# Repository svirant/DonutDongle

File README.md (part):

# Donut Dongle

**Arduino Nano based hub that connects your digital and analog console switching setup with the RetroTink 4K and/or RetroTink 5x / OSSC for Auto Profile switching** </br>

The Donut Dongle connects to a switch in a way that allows it to see which port is active. When a console powers on (auto-switching) or an input is manually selected, the Donut Dongle sends a serial command to the RetroTink 4k (or IR signal to the RT5x, OSSC) telling it to load a profile. For the RT4K, the profiles can either be defined as remote profiles; those configured in the menu for the remote buttons. Or they can be SVS profiles which are configured on the RT4K's SDcard. <br />

For details, refer to the ["How to Use"](https://github.com/svirant/DonutDongle/tree/main/README.md#how-to-use) section below.

> [!TIP]
> If DIY is not your thing. I have assembled versions for gScart/gComp and MT-VIKI/TESmart/Extron/db9 available in my [Ko-fi](https://ko-fi.com/donutswdad/shop) shop.
</br>

> [!NOTE]
> *NEW* version allows:
>   - **Alternate SVS Profile System** - allows a different set of profiles to load. Explained in the ["New IR Remote Control functionality"](https://github.com/svirant/DonutDongle#new-ir-remote-control-functionality) section below.
>   - **Fallback** - feature that allows a switch that reports having no active inputs to change profiles over to one that does.
>   - **MT-VIKI Disconnection Detection** - when an input is powered off and on, the profile is resent.
>     - **Disable MT-VIKI beeping by pressing the "#" button on its remote.**
>   - **front case buttons/remote NOW change profiles on the MT-VIKI HDMI switch.** Thanks to [Arthrimus](https://scalablevideoswitch.com/)! 
>   - **auto-switching on Extron Matrix switchers** that support DSVP. Works with RGBS/HV and HDMI/DVI signal types.
>   - **Support for older Extron Crosspoint (non plus) matrix switchers**
> <br />
> 
> <br /> Use the follow Options to enable:
> ```
> #define automatrixSW1 true  // set true for auto matrix switching on "SW1" port
> #define automatrixSW2 false // set true for auto matrix switching on "SW2" port
>
> uint8_t const ExtronVideoOutputPortSW1 = 1; // For non "Plus" Extron Matrix models, must specify video output port that connects to RT4K
> uint8_t const ExtronVideoOutputPortSW2 = 1;
> 
> uint8_t const vinMatrix[65] = {0,  // MATRIX switchers  // When auto matrix mode is enabled: (automatrixSW1 / SW2 defined above)
>                                                        // set to 0 for the auto switched input to tie to all outputs
>                                                        // set to 1 for the auto switched input to trigger a Preset
>                                                        // set to 2 for the auto switched input to tie to "ExtronVideoOutputPortSW1" / "ExtronVideoOutputPortSW2"
>                                                        //
>                                                        // For option 1, set the following inputs to the desired Preset #
>                                                        // (by default each input # is set to the same corresponding Preset #)
>                                                       
> ```
<br />

### [More Images...](https://photos.sixteenbit.app/share/KXUwNPO2uvjenoCdj3gsQnEMd4q5h4ymUv-0fc8PItIhjA8JXHlVgPDeFnTRXM76KPM)

<br />

# Thanks to 
 - [Justin Peacock](https://byjustin.me/) for the amazing case design
 - HerraAAV3 from the RetroTink discord for the VGA Adapter case design
 - [Mike Chi](https://retrotink.com) for help with the open drain serial bits
 - [@niquallis](https://x.com/niquallis), [@UstSte](https://x.com/UstSte), and last but not least [Aru](https://x.com/CielFricker249) for beta testing

<br />

# Supported Switches
(current list, but not limited to)
| **Switch**    | Supported | Notes |
| ------------- | ------------- |------------- |
| MT-VIKI 8 port HDMI | yes, confirmed first hand. RT4K remote can also change inputs and profiles.  | Front case buttons and included IR remote also change profiles! **Disable MT-VIKI beeping by pressing the "#" button on its remote.** |
| TESmart 16x1 HDMI  | yes, confirmed first hand  | RT4K remote can also change inputs and profiles. |
| TESmart 8x1 HDMI  | unconfirmed, but should work, let me know! ||
| gSCARTsw / gCOMPsw | **version 5.x** confirmed by [@niquallis](https://x.com/niquallis) and [@UstSte](https://x.com/UstSte), thanks so much for your help! | Manual input selection works too! |
| Extron RGBHV sw6  | yes, confirmed first hand  | |
| Extron DXP 88 | yes, confirmed first hand | Auto-switching can be enabled in "Options" section of .ino.  Works with Presets. On SW1, Preset 1 is S1_ profile. On SW2, Preset 1 is S101_ profile, etc. <br><br>Power up the switch before connecting the DonutHole. |
| Extron CrossPoint, MVX, etc | yes, confirmed by other users | Auto-switching can be enabled for switches that supports DSVP and are RGBS/HDMI/DVI signal types. By default, works with Presets as shown in the Note above. |
| Extron CrossPoint E-series  | yes, works with Presets and Input changes | Must set ExtronVideoOutputPortSW1 / SW2 variable to output connected to RT4K |
| Extron SW4 VGA Ars | yes, confirmed by "Nobody" on the RT4K Discord |
| Otaku Games Scart 10 | Jumper moved to "L" and with required [mod](https://github.com/svirant/RT4k_HD15_serial_control/tree/main/Otaku%20Games%20Scart%20Switch) , **SVS=0; must also be set in the Otaku .ino for the DD to respond** | modded switch works on its own, but connecting through the DD is mostly useful if your Otaku mod doesn't include the buffer IC |

<br />

# Connections
  - Connect 4 switches Total
    - 2x gscart/gcomp
    - 2x Extron, 2x TESmart, or 1 of each
  - 1x usb-c port for power/programming (on Arduino Nano)
  - 1x 3.5mm "TX OUT to Retrotink 4K VGA adapter" port
  - 1x IR Emitter (required for OSSC, RT5x (RT5x must be on firmware version 3.7 or higher))
  - 1x IR Receiver (optional for better reception and IR remote customizations)

<br /><br />

# Layout Example
 - **TESmart 16x1 HDMI switch & 2x gSCART/gCOMP**
    - **VGA Passthrough adapter**
    - **TESmart adapter**
    - **gScart EXT pushpin adapter**

<br />
<br />

 - **Case closed**
   - **ribbon cables fold over and come out slots in the back of case**

<br /><br />

# Connection Acccessories

**gscart/gcomp EXT connector (plug-n-play)**<br />
The spring pins allow it to stay "sandwiched" in place by the lid<br />

<br />

**TESmart connector**<br />

**MT-VIKI / Extron / DB9 adapter**<br />

**Parts listed in [BOM](https://github.com/svirant/DonutDongle/tree/main/README.md#connection-accessories) below**

**Alternate Extron connection type:**
   - **DB9 male to 3.5mm (connects to alt sw1 / alt sw2 port instead of 2x5 header)**
   - **Higher quality and much longer cord than the standard 2x5 cable**

----------------
# New IR Remote Control functionality
When using the optional IR Receiver, the IR reception of the RT4K can be been greatly enhanced. You can think of it as an IR repeater, but instead talks to the RT4K via Serial for solid communication. Since the Donut Dongle is in the middle, other remote features can be added such as:
 - **Alternate SVS Profiles**: Have you ever wanted to add CRT effects to all of your existing SVS profiles? Or wanted all your profiles to output at 1080p instead of 4K? With this feature you can create a set of SVS profiles that have these changes and activate the system with the remote. Pressing the "SAFE" button twice + 1 - 9 buttons will allow you to configure 9 different sets of these profiles per regular profile to load instead of the regular one you created. For example: Instead of SVS profile S1_SNES.rt4 loading, S1001_SNES.rt4 will load instead after activating with the "SAFE"x2 + 1 button. Here are some more examples so you can see the pattern used for creating these: </br>

    "SAFE"x2 + x button = Sx001_SNES-CRT.rt4, where x is the number button selected and 001 is the S1_ profile represented in 3 digits. </br>
    "SAFE"x2 + 2 button = S2001_SNES-1080p.rt4 </br>
    "SAFE"x2 + 3 button = S3001_SNES-Zoomed.rt4 </br>
    "SAFE"x2 + 4 button = S4001_SNES.rt4 </br>
    "SAFE"x2 + 5 button = S5001_SNES.rt4 </br>
    "SAFE"x2 + 6 button = S6001_SNES.rt4 </br>
    "SAFE"x2 + 7 button = S7001_SNES.rt4 </br>
    "SAFE"x2 + 8 button = S8001_SNES.rt4 </br>
    "SAFE"x2 + 9 button = S9001_SNES.rt4 </br> 

   - The name following the "\_" can be changed as well. So a name like S1001_SNES-CRT.rt4 can be used to better describe. Only the naming pattern before the "\_" is important. </br>

   - When SVS profile S2 normally would load, Sx002 would load instead where x = the number button chosen prior and 002 represents the S2 profile. S2100_NES.rt4 for example would be the 2nd Alternate profile for S100_NES.rt4. It's up to you to create these alternate sets of profiles on your SD card of course. To disable this feature and return to your normally configured profiles, press "SAFE"x2  + 10, 11, or 12 buttons on the remote.

 - SAFE button once + profile button 1 - 12 loads SVS profiles of your choosing. By default is SVS 1 - 12. Configured with auxprof[] in the Settings section of the .ino
  
 - Normally, if you power on your console before waking the RT4K, the RT4K will have not seen the profile change. Using the remote's POWER button, in this configuration, will wake the RT4K "and" resend the profile after it's finished waking.

 - AUX8 button + Power button power cycles your TV via IR Emitter. (only LG OLED CX atm, more can be added upon request)

 - AUX8 pressed twice, manually enter a SVS profile to load with the profile buttons using 1 - 9 and 10,11,12 buttons for 0. Must use 3 digits. Ex: 001 = 1, 010 = 10, etc

 - AUX8 pressed 3x will perform the standard AUX8 action
 
 - MT-ViKI 8 Port HDMI switch's inputs can be changed. Must configure "MTVir" in the options section of the .ino
    - AUX7 + button 1 - 8 for inputs 1 - 8 on "alt sw1" port (SVS profiles 1 - 8)
    - AUX8 + button 1 - 8 for inputs 1 - 8 on "alt sw2" port (SVS profiles 101 - 108)

 - TESmart 16x1 HDMI switch's inputs can changed. Must set "TESmartir" in the options section.
    - AUX7 + button 1 - 12, aux1, aux2, aux3, aux4 for inputs 1 - 16 on "alt sw1" port (SVS profiles 1 - 16)
    - AUX8 + button 1 - 12, aux1,aux2,aux3,aux4 for inputs 1 - 16 on "alt sw2" port (SVS profiles 101 - 116)

**gScart / gComp Control** (must set gctl = 1 in Options, Only supported on vers 5.x switches)

 - AUX5 button + profile button 1 - 8 button selects corresponding input on gscart sw1
    - AUX5 button + profile button 9 - 12 button to return to auto switching

 - AUX6 button + profile button 1 - 8 button selects corresponding input on gscart sw2
    - AUX6 button + profile button 9 - 12 button to return to auto switching

 - RT5x and OSSC may require a repeat of the button combos
 
 <br />

Let me know what ideas you have, and perhaps I can add them in.

**Note:** To stop the RT4K from responding twice (once from the built-in IR sensor and once from the Donut Dongle), place the included "ir_remote.txt" on the root of the SDcard. This remaps the builtin IR for every button except POWER to the RT5x remote. This way you can still use the POWER button to power on the RT4K but will stop it from responding from all other button presses.

# Ordering PCBs
PCBs for this project:
 - [Donut Dongle](https://github.com/svirant/DonutDongle/blob/main/RT4K_donut_dongle.zip)
 - [VGA Adapter](https://github.com/svirant/DonutDongle/tree/main/Adapters) (VGAPassthrough or YC2VGA)
 - (Optional) [TESmart_connector](https://github.com/svirant/DonutDongle/tree/main/Accessories)
 - (Optional) [gscart_ext_connector](https://github.com/svirant/DonutDongle/tree/main/Accessories) (works for gcomp too!)
 
There are plenty of options for PCB manufacturing but I prefer [JLCPCB](https://jlcpcb.com) (No affiliation). Using the gerber (.zip) files provided, it's easy to place an order. Below are some tips/guidelines:
- 1.0mm PCB Thickness for gscart_ext_connector.zip
- 1.6mm for all others
- For Surface Finish, "HASL(with lead)" is fine
- 4 Layer PCBs are the same cost as 2 Layer for the VGA Adapters. Because of that, the inner 2 layers are being used as ground planes for better EMI protection. Thanks to https://x.com/zaxour for the idea!
- "Remove Mark" option is now free on JLCPCB. Use it!
- All remaining default options should be fine
- Let me know if you have any questions!

# Assembly
**v1.0**<br /><br />
[Interactive HTML BOM](https://svirant.github.io/DonutDongle/images/ibom.html)

# (2M) baud mod
- **NOT supported with SVS connected to VGA adapter**
  - ...unless SDA/SDL trace is cut on VGA Adapter, but that disables the SVS's profile sending.
  - SVS runs at 9600 baud which conflicts with 2M regardless.
  - Extra Tx/Rx wire length of VGA cable can also cause issues. Workaround - You can cut SDA/SDL traces on the bottom of the VGA adapter to continue passing video but disables "VGA cable Serial" passthrough. (How the SVS sends profile changes)

  <br>
- Replace R10 (10K) with a 2.2K resistor
- Remove R9 and bridge pads
- Connect R1 and R9 as shown with a 2.2K resistor
<br><br>

# PCB
**v1.0**

<br /><br />

# Schematic
**v1.0**

<br /><br />

## Bill of Materials (BOM)
### [- 3D Printed Dount Dongle Case](https://makerworld.com/en/models/1154283#profileId-1159282)
### [- 3D Printed VGA Adapter Case](https://github.com/svirant/DonutDongle/tree/main/Adapters) [Courtesy of HerraAAV3 on the RetroTink Discord]
### [- Digikey shared list](https://www.digikey.com/en/mylists/list/53XEHTQZJK)
### [- AliExpress wish list](https://www.aliexpress.com/p/wish-manage/share.html?smbPageCode=wishlist-amp&spreadId=09A40E28BA67E42DE9AF29A70E7238263DE305046632ABE9A0D5E1C5C4589AD9)
<br />

* **Donut Dongle PCB**

| **Qty**    | Designation | Part |  Link  |  Notes |
| ------------- | ------------- |------------- |------------- |------------- |
| 2  | C1,C5 | 0.1 uf / 100nf 50V X7R 0805 Capacitor| [Digikey](https://www.digikey.com/en/products/detail/yageo/CC0805KRX7R9BB104/302874?s=N4IgTCBcDaIMwEYEFokBYAMrkDkAiIAugL5A) | |
| 3  | C2-C4 | 0.33 uf / 330nf 50V X7R 0805 Capacitor| [Digikey](https://www.digikey.com/en/products/detail/samsung-electro-mechanics/CL21B334KBFNNNE/3886781) | |
| 1  | R1 | 30 OHM 1% 1/2W 0805 Resistor | [Digikey](https://www.digikey.com/en/products/detail/panasonic-electronic-components/ERJ-P06F30R0V/9811718) | |
| 1  | R2 | 1K OHM 1% 1/8W 0805 Resistor | [Digikey](https://www.digikey.com/en/products/detail/yageo/RC0805FR-071KL/727444) | |
| 10  | R3 - R10, R17, R19 | 10K OHM 1% 1/8W 0805 Resistor | [Digikey](https://www.digikey.com/en/products/detail/yageo/AC0805FR-0710KL/2827834) | |
| 8  | R11 - R16, R18, R20 | 20K OHM 1% 1/8W 0805 Resistor | [Digikey](https://www.digikey.com/en/products/detail/yageo/RC0805FR-0720KL/727720) | |
| 1  | Q1 | 2N3904 NPN Transistor | [AliExpress](https://www.aliexpress.us/item/3256806623522970.html) | |
| 1  | U1 | MAX3232 SOP-16 RS-232 Interface IC | [AliExpress](https://www.aliexpress.us/item/3256807314260762.html) | |
| 1  | U2 | IC BUF NON-INVERT 5.5V SOT23-6 | [Digikey](https://www.digikey.com/en/products/detail/texas-instruments/SN74LVC2G07DBVR/486427) or [alternate](https://www.digikey.com/en/products/detail/umw/SN74LVC2G07DBVR/24889644)| |
| 1  | PH1 | PJ-307 3.5mm Stereo Jack | [AliExpress](https://www.aliexpress.us/item/3256805624175150.html) | |
|    | |  or **1x** 3.5mm Audio Jack Socket | [AliExpress](https://www.aliexpress.us/item/2251832685563184.html) | Like the PJ-307 but missing the inner 2 poles which arent needed anyways |
| 4  | J4,J9-11 | PJ-320 3.5MM Headphone Jack Audio Video Female | [AliExpress](https://www.aliexpress.us/item/3256807448104402.html) | Color: PJ-320B DIP | 
| 2  | J3,J6 | 2x5 Pin Double Row 2.54mm Pitch Straight Box Header | [AliExpress](https://www.aliexpress.us/item/3256805177947724.html) | (Color: STRAIGHT TYPE, Pins: 10PCS DC3-10Pin) |
| 2  | J5,J8 | 2x4 Pin Double Row 2.54mm Pitch Straight Box Header | [AliExpress](https://www.aliexpress.us/item/3256805177947724.html) | (Color: STRAIGHT TYPE, Pins: 10PCS DC3-8Pin) |
| 1  | (optional) | 3.5mm CHF03 1.5 Meters IR Infrared Remote Emission Cable | [AliExpress](https://www.aliexpress.us/item/3256805962345169.html) | required for OSSC, RT5X (must be firmware version 3.7+) |
| 1  | (optional) | 3.5mm Infrared Remote Control Receiver Extension Cable | [AliExpress](https://www.aliexpress.us/item/2251832741040177.html) | required for [New IR Remote Control functionality](https://github.com/svirant/DonutDongle?tab=readme-ov-file#new-ir-remote-control-functionality) |
| 2  | H1,H2 | 2.54mm Pitch Single Row Female 15P Header Strip | [AliExpress](https://www.aliexpress.us/item/3256801232229618.html) | |
| 1  | | Any 3.5mm / aux / stereo / trs / cable | [AliExpress](https://www.aliexpress.us/item/2255799962255486.html) | |
| 1  | | usb-c cable for Arduino power & initial programming | [AliExpress](https://www.aliexpress.us/item/3256806983355947.html) | |
| 1  | | Arduino Nano type c | Support [RetroRGB!](https://amzn.to/4gnHqN4) | Make sure the headers and esp the 2x3 pins are not soldered. |
| 1  | JP2 | 2x3 Pin Double Row 2.54mm Pitch Header | | Use the one that comes with the Arduino Nano. Jumper "H" for all switches unless instructed otherwise. |
| 2  | JP3,4 | 1x3 Pin Single Row 2.54 Pitch Header | | Dont buy two 1x3. Find any single row header and break off two 1x3 sections. Jumper "H" for all switches unless instructed otherwise. |
| 4  | | 2.54mm Jumper | [AliExpress](https://www.aliexpress.us/item/2255800354403384.html) | You can also just solder blob "H". "L" jumper setting has only 1 use case atm. |

* **Switch connection Cables**

| **Qty**    | Switch Type | Part |  Link  |  Notes |
| ------------- | ------------- |------------- |------------- |------------- |
| 1 or 2 | **TESmart HDMI** | Any 3.5mm / aux / stereo / trs / Cable | [AliExpress](https://www.aliexpress.us/item/2255799962255486.html) | strip 1 end to expose red(Rx)/white(Tx)/gnd wires for the green screw clamp OR use the TESmart_connector shown below|
| 1 or 2 | **GscartSW/GCompSW** | 2x4 Pin Double Row 2.54 Pitch Angled Box Header | [AliExpress](https://www.aliexpress.us/item/3256805177947724.html?) | (Color: RIGHT ANGLE TYPE, Pins: 10PCS DC3 8Pin), Solders onto EXT port. Or use the gscart_ext_connector shown below.  |
|1 or 2 | **GscartSW/GCompSW** | 2x4 Pin Female Header Ribbon Cable | [AliExpress](https://www.aliexpress.us/item/3256804576275377.html?) | (Pins: 2x4Pin, Color: Any length) |
| 1  | **Extron** | 2 Port DB9 to 2x5 Pin Female Header Ribbon Cable | [AliExpress](https://www.aliexpress.us/item/3256807472891897.html) | |
| | | or **2x** DB9 Male to 3.5mm Male Serial RS232 Cable 6feet | [Amazon](https://www.amazon.com/LIANSHU-DC3-5mm-Serial-RS232-Cable/dp/B07G2ZL3SL/) | "MUST" be wired as so: [DB9 Male Pin 5 -> Sleeve, DB9 Male Pin 2 -> Tip, DB9 Male Pin 3 -> Ring](/images/7.png) |
| | | **or** make your own connectors in the "[Connection Accessories](https://github.com/svirant/DonutDongle?tab=readme-ov-file#connection-accessories-optional)" section below. | | |

### At least 1 of the following [VGA adapters](https://github.com/svirant/DonutDongle/tree/main/Adapters) is required:

* **YC2VGA w/ Serial Tap v2: (enhanced s-video and composite as a bonus)**

<br />

| **Qty**    | Part |  Link  |  Notes |
| ------------- | ------------- |------------- |------------- |
| 1  | Yellow RCA Composite jack | [AliExpress](https://www.aliexpress.us/item/3256805949533421.html) | (Color: Yellow) |
| 1  | S-Video jack | [AliExpress](https://www.aliexpress.us/item/3256804041313042.html) | (Color: A 4Pin) |
| 1  | PJ-320 3.5MM Headphone Jack Audio Video Female | [AliExpress](https://www.aliexpress.us/item/3256805995568762.html) | (Color: 10PCS PJ-320) |
| 1  | VGA Male Connector [L717HDE15PD4CH4R-ND] | [Digikey](https://www.digikey.com/en/products/detail/amphenol-cs-commercial-products/L717HDE15PD4CH4R/4886543) | |
 
* **VGA Passthrough w/ Shared Serial Tap:**
   - Confirmed compatible with the Scalable Video Switch and it's auto profiles.

<br />

<br />

| **Qty**    | Part |  Link  |  Notes |
| ------------- | ------------- |------------- |------------- |
| 1 | VGA Male Connector [L717HDE15PD4CH4R-ND] | [Digikey](https://www.digikey.com/en/products/detail/amphenol-cs-commercial-products/L717HDE15PD4CH4R/4886543) | |
| 1 | VGA Female Connector | [AliExpress](https://www.aliexpress.us/item/3256807197056325.html) | (Color: DB15 3.08) |
| 1 | PJ-320 3.5MM Headphone Jack Audio Video Female | [AliExpress](https://www.aliexpress.us/item/3256805995568762.html) | (Color: 10PCS PJ-320) |
| 2 | #4-40 x 3/4" screw (optional) | [Ebay](https://www.ebay.com/itm/222577369468) | |

  ### [Connection Accessories](https://github.com/svirant/DonutDongle/tree/main/Accessories) (optional)

  * **gscart/gcomp EXT connector**

| **Qty**    | Part |  Link  |  Notes |
| ------------- | ------------- |------------- |------------- |
| 1 | 2x4 Pin Double Row 2.54 Pitch Angled Box Header | [AliExpress](https://www.aliexpress.us/item/3256805177947724.html?) | (Color: RIGHT ANGLE TYPE, Pins: 10PCS DC3 8Pin) |
| 6 | Pogo-Pin | [Digikey](https://www.digikey.com/en/products/detail/mill-max-manufacturing-corp/0906-1-15-20-75-14-11-0/1147049) | |
   
  * **TESmart connector**

 | **Qty**    | Part |  Link  |  Notes |
| ------------- | ------------- |------------- |------------- |
| 1 | PJ-320 3.5MM Headphone Jack Audio Video Female | [AliExpress](https://www.aliexpress.us/item/3256805995568762.html) | (Color: 10PCS PJ-320) |

  * **MT-VIKI / Extron / DB9 connector**

 | **Qty**    | Part |  Link  |  Notes |
| ------------- | ------------- |------------- |------------- |
| 1 | PJ-320 3.5MM Headphone Jack Audio Video Female | [AliExpress](https://www.aliexpress.us/item/3256805995568762.html) | (Color: 10PCS PJ-320) |
| 1 | DB9 Male connector | [AliExpress](https://www.aliexpress.us/item/3256805749759770.html?) | (Color: Male head) |
| 2 | #4-40 1/4" pan head screw | [Amazon](https://www.amazon.com/dp/B00F34USTG?) | |

  -----------
# Programming an Arduino Nano
I recommend the [Official Arduino IDE and guide](https://www.arduino.cc/en/software/) if you're unfamiliar with Arduinos. All .ino files used for programming are listed above. The following Libraries will also need to be added in order to Compile successfully.<br />
- **Libraries:**
  - <IRremote.hpp> "IRremote" available through the built-in Library Manager under "Tools" -> "Manage Libraries..."
  - <AltSoftSerial.h>  Follow these steps to add AltSoftSerial.h
    - Goto https://github.com/PaulStoffregen/AltSoftSerial
    - Click the GREEN "<> Code" box and "Download ZIP"
    - In Arduino IDE; goto "Sketch" -> "Include Library" -> "Add .ZIP Library"
   
## Steps to program the Donut Dongle
 - 1 - Click the green "<> Code" button above and "Download ZIP".
 - 2 - Extract the .zip file and open up the "Donut_Dongle.ino" file in the Arduino IDE. It will ask if you would like to move this file inside a folder, select OK.
 - 3 - With the source code now open, select "Tools" -> "Board" -> "Arduino AVR Boards" -> "Arduino Nano"
 - 4 - Connect the Donut Dongle device to your PC or Mac using the usb-c cable. You should see an LED light up when connected.
 - 5 - With the Donut Dongle now connected, select it's "port" by going to "Tools" -> "Port", and select the port that starts with "/dev/cu.usbserial-" (on Mac) or "COM" if on PC.
 - 6 - From the menu at the top, select "Sketch" -> "Verify/Compile". If everything is setup properly, you should see a message in the bottom corner saying "Done compiling".
 - 7 - Now select "Sketch" -> "Upload". You should see the LEDs on the Donut Dongle flicker and a message that says "Done uploading." if successful.
   - If you get errors, see the section below about changing the "Bootloader" type.
 - 8 - Disconnect the usb-c cable from your computer and give it a whirl! You can repeat these steps in the future to make any other changes or update if a newer firmware is ever released.
 - 9 - It's also best practice when unplugging/reconnecting cables to the Donut Dongle, that you do so with the power disconnected. 
<br>

  -----------
# How to Use
- Make sure **"Auto Load SVS"** is **"On"** under the RT4K Profiles menu.  
- The RT4K checks the **/profile/SVS** subfolder for profiles and need to be named: **S\<input number>_\<user defined>.rt4**  For example, SVS input 2 would look for a profile that is named S2_SNES.rt4.  If there’s more than one profile that fits the pattern, the first match is used.

- Check the RT4K Diagnostic Console for Serial commands being received as confirmation.

  -----------
# Troubleshooting
 - When (un)plugging aux cables from "alt sw1" or "alt sw2" ports make sure Donut Dongle power is disconnected. Sometimes the onboard MAX3232 chip can lock up if this is not done.
   - To fix lockup, power off switch and DD (Donut Dongle). Disconnect/reconnect aux cable from DD and power up switch first, then DD last.
  
 - Some Arduino Nanos come with an Old Bootloader and won't Upload unless specified. **If you get errors** when trying to upload, swap to this option as a possible fix.

  -----------
## SVS Profile numbering scheme

| **SVS = 1 (default)** | **Profile #** | Notes |
|----------|----------|---------|
| Extron sw1 / alt sw1 | 1 -  99 | also for TESmart, MT-ViKi, Otaku Games Scart 10 devices|
| Extron sw2 / alt sw2 | 101 - 199 | also for TESmart, MT-ViKi, Otaku Games Scart 10 devices |
| GSCART sw1 | 201 - 208 | |
| GSCART sw2 | 209 - 216 | |

Remote Button Profiles are **not** used when **SVS=1**

<br />

| **SVS = 0** | **Profile #** | Notes |
|----------|----------|---------|
| Extron sw1 / alt sw1 | 13 -  99 | also for TESmart, MT-ViKi, Otaku Games Scart 10 devices|
| Extron sw2 / alt sw2 | 101 - 199 | also for TESmart, MT-ViKi, Otaku Games Scart 10 devices |
| GSCART sw1 | 201 - 208 | |
| GSCART sw2 | 209 - 216 | |

Remote Button Profiles **1-12** are used for Extron sw1 when **SVS=0**

<br />

| **SVS = 2** | **Profile #** | Notes |
|----------|----------|---------|
| Extron sw1 / alt sw1 | 1 -  99 | also for TESmart, MT-ViKi, Otaku Games Scart 10 devices|
| Extron sw2 / alt sw2 | 101 - 199 | also for TESmart, MT-ViKi, Otaku Games Scart 10 devices |
| GSCART sw1 | N/A | |
| GSCART sw2 | 213 - 216 | inputs 5-8 |

Remote Button Profiles **1-12** are used for GSCART sw1 inputs **1-8** and GSCART sw2 inputs **1-4** when **SVS=2**

<br />

----------------

The following is from the .ino file itself. Refer to it directly for all **Advanced Options**.
```
/*
////////////////////
//    OPTIONS    //
//////////////////
*/

uint8_t const debugE1CAP = 0; // line ~495
uint8_t const debugE2CAP = 0; // line ~768
uint8_t const debugState = 0; // line ~432

uint16_t const offset = 0; // Only needed for multiple Donut Dongles (DD). Set offset so 2nd,3rd,etc boards don't overlap SVS profiles. (e.g. offset = 300;) 
                      // MUST use SVS=1 on additional DDs. If using the IR receiver, recommended to have it only connected to the DD with lowest offset.

uint8_t const SVS = 1; //     "Remote" profiles are profiles that are assigned to buttons 1-12 on the RT4K remote. "SVS" profiles reside under the "/profile/SVS/" directory 
                      //     on the SD card.  This option allows you to choose which ones to call when a console is powered on.  Remote profiles allow you to easily change 
                      //     the profile being used for a console's switch input if your setup is in flux. SVS require you to rename the file itself on the SD card which is 
                      //     a little more work.  Regardless, SVS profiles will need to be used for console switch inputs over 12.
                      //
                      // **** Make sure "Auto Load SVS" is "On" under the RT4K Profiles menu. A requirement for most options ****
                      //
                      // 0 - use "Remote" profiles 1-12 for up to 12 inputs on 1st Extron Switch and SVS 13 - 99 for everything over 12. Only SVS profiles are used on 2nd Extron Switch if connected.
                      //
                      //     - remote profiles 1-12 for 1st Extron or TESmart Switch (If S0 below is set to true - remote profile 12 is used when all ports are in-active)
                      //     - SVS  12 - 99  for 1st Extron or TESmart (S0 is true)
                      //     - SVS  13 - 99  for 1st Extron or TESmart (S0 is false)
                      //     - SVS 101 - 199 for 2nd Extron or TESmart
                      //     - SVS 201 - 208 for 1st gScart
                      //     - SVS 209 - 216 for 2nd gScart
                      //
                      // 1 - use only "SVS" profiles.
                      //     Make sure "Auto Load SVS" is "On" under the RT4K Profiles menu
                      //     RT4K checks the /profile/SVS subfolder for profiles and need to be named: "S<input number>_<user defined>.rt4"
                      //     For example, SVS input 2 would look for a profile that is named S2_SNES.rt4
                      //     If there’s more than one profile that fits the pattern, the first match is used
                      //
                      //     - SVS   1 -  99 for 1st Extron or TESmart
                      //     - SVS 101 - 199 for 2nd Extron or TESmart
                      //     - SVS 201 - 208 for 1st gScart
                      //     - SVS 209 - 216 for 2nd gScart
                      //     - SVS   0       for S0 option mentioned below
                      //
                      //  ** If S0 below is set to true, create "/profile/SVS/S0_<user defined>.rt4" for when all ports are in-active. Ex: S0_HDMI.rt4
                      //
                      // 2 - use "Remote" profiles 1-12 for gscart/gcomp switches. Remote profile 1-8 for 1st gscart switch, 9-12 for inputs 1-4 on 2nd gscart switch.
                      //     inputs 5-8 on the 2nd gscart switch will use SVS profiles 213 - 216
                      //
                      //     - remote profiles 1-8 for 1st gScart, 9 - 12 for first 4 inputs on 2nd gScart (If S0 below is set to true - remote profile 12 is used when all ports are in-active)
                      //     - SVS 213 -  216 for remaining inputs 5 - 8 on 2nd gScart 
                      //     - SVS   1 -  99 for 1st Extron or TESmart
                      //     - SVS 101 - 199 for 2nd Extron or TESmart
                      //

bool const S0 = false;  // (Profile 0) default is false
                         //
                         //  ** Recommended to remove any /profile/SVS/S0_<user defined>.rt4 profiles and leave this option set false if using in tandem with the Scalable Video Switch. **
                         //  ** Does not work with TESmart HDMI switches **
                         //
                         // For SVS=0; set true to load "Remote Profile 12" when all ports are in-active on SW1 (and SW2 if connected). 
                         // You can assign it to a generic HDMI profile for example.
                         // If your device has a 12th input, SVS will be used instead. "If" you also have an active 2nd Extron Switch, Remote Profile 12
                         // will only load if "BOTH" switches have all in-active ports.
                         // 
                         // For SVS=1, /profile/SVS/ "S0_<user defined>.rt4" will load instead of Remote Profile 12
                         //
                         // For SVS=2, Remote Profile 12 will be used instead of "S0_<user defined>.rt4"
                         //

////////////////////////// 
                        // Choosing the above two options can get quite confusing (even for myself) so maybe this will help a little more:
                        //
                        // when S0=0 and SVS=0, button profiles 1 - 12 are used for EXTRON sw1, and SVS for EVERYTHING else
                        // when S0=0 and SVS=1, SVS profiles are used for everything
                        // when S0=0 and SVS=2, button profiles 1 - 8 are used for GSCART sw1, 9 - 12 for GSCART sw2 (ports 1 - 4), and SVS for EVERYTHING else
                        // when S0=1 and SVS=0, button profiles 1 - 11 are used for EXTRON sw1 and Remote Profile 12 as "Profile S0", and SVS for everything else 
                        // when S0=1 and SVS=1, SVS profiles for everything, and uses S0_<user defined>.rt4 as "Profile 0" 
                        // when S0=1 and SVS=2, button profiles 1 - 8 are used for GSCART sw1, 9 - 11 for GSCART sw2 (ports 1 - 3) and Remote Profile 12 as "Profile S0", and SVS for EVERYTHING else
                        //
//////////////////////////

// For Extron Matrix switches that support DSVP. RGBS and HDMI/DVI video types.

#define automatrixSW1 false // set true for auto matrix switching on "SW1" port
#define automatrixSW2 false // set true for auto matrix switching on "SW2" port

///////////////////////////////

uint8_t const ExtronVideoOutputPortSW1 = 1; // For certain Extron Matrix models, must specify the video output port that connects to RT4K
uint8_t const ExtronVideoOutputPortSW2 = 1; // can also be used for auto matrix mode as shown in next option

///////////////////////////////

uint8_t const vinMatrix[65] = {0,  // MATRIX switchers  // When auto matrix mode is enabled: (automatrixSW1 / SW2 defined above)
                                                        // set to 0 for the auto switched input to tie to all outputs
                                                        // set to 1 for the auto switched input to trigger a Preset
                                                        // set to 2 for the auto switched input to tie to "ExtronVideoOutputPortSW1" / "ExtronVideoOutputPortSW2"
                                                        //
                                                        // For option 1, set the following inputs to the desired Preset #
                                                        // (by default each input # is set to the same corresponding Preset #)
                           1,  // input 1 SW1
                           2,  // input 2
                           3,  // input 3
                           4,  // input 4
                           5,  // input 5
                           6,  // input 6
                           7,  // input 7
                           8,  // input 8
                           9,  // input 9
                           10,  // input 10
                           11,  // input 11
                           12,  // input 12
                           13,  // input 13
                           14,  // input 14
                           15,  // input 15
                           16,  // input 16
                           17,  // input 17
                           18,  // input 18
                           19,  // input 19
                           20,  // input 20
                           21,  // input 21
                           22,  // input 22
                           23,  // input 23
                           24,  // input 24
                           25,  // input 25
                           26,  // input 26
                           27,  // input 27
                           28,  // input 28
                           29,  // input 29
                           30,  // input 30
                           30,  // input 31
                           30,  // input 32
                               //
                               // ONLY USE FOR 2ND MATRIX SWITCH on SW2
                           1,  // 2ND MATRIX SWITCH input 1 SW2
                           2,  // 2ND MATRIX SWITCH input 2
                           3,  // 2ND MATRIX SWITCH input 3
                           4,  // 2ND MATRIX SWITCH input 4
                           5,  // 2ND MATRIX SWITCH input 5
                           6,  // 2ND MATRIX SWITCH input 6
                           7,  // 2ND MATRIX SWITCH input 7
                           8,  // 2ND MATRIX SWITCH input 8
                           9,  // 2ND MATRIX SWITCH input 9
                           10,  // 2ND MATRIX SWITCH input 10
                           11,  // 2ND MATRIX SWITCH input 11
                           12,  // 2ND MATRIX SWITCH input 12
                           13,  // 2ND MATRIX SWITCH input 13
                           14,  // 2ND MATRIX SWITCH input 14
                           15,  // 2ND MATRIX SWITCH input 15
                           16,  // 2ND MATRIX SWITCH input 16
                           17,  // 2ND MATRIX SWITCH input 17
                           18,  // 2ND MATRIX SWITCH input 18
                           19,  // 2ND MATRIX SWITCH input 19
                           20,  // 2ND MATRIX SWITCH input 20
                           21,  // 2ND MATRIX SWITCH input 21
                           22,  // 2ND MATRIX SWITCH input 22
                           23,  // 2ND MATRIX SWITCH input 23
                           24,  // 2ND MATRIX SWITCH input 24
                           25,  // 2ND MATRIX SWITCH input 25
                           26,  // 2ND MATRIX SWITCH input 26
                           27,  // 2ND MATRIX SWITCH input 27
                           28,  // 2ND MATRIX SWITCH input 28
                           29,  // 2ND MATRIX SWITCH input 29
                           30,  // 2ND MATRIX SWITCH input 30
                           30,  // 2ND MATRIX SWITCH input 31
                           30,  // 2ND MATRIX SWITCH input 32
                           };

                           // ** Must be on firmware version 3.7 or higher **
uint8_t const RT5Xir = 0;     // 0 = disables IR Emitter for RetroTink 5x
                              // 1 = enabled for Extron sw1 / alt sw1, TESmart HDMI, MT-ViKi, or Otaku Games Scart Switch if connected
                              //     sends Profile 1 - 10 commands to RetroTink 5x. Must have IR LED emitter connected.
                              //
                              // 2 = enabled for gscart switch only (remote profiles 1-8 for first gscart, 9-10 for first 2 inputs on second gscart)
                              //
                              // 3 = enabled for Extron sw2 / alt sw2, TESmart HDMI, MT-ViKi, or Otaku Games Scart Switch if connected 
                              //     sends Profile 1 - 10 commands to RetroTink 5x. Must have IR LED emitter connected.

uint8_t const OSSCir = 0;     // 0 = disables IR Emitter for OSSC
                              // 1 = enabled for Extron sw1 switch, TESmart HDMI, or Otaku Games Scart Switch if connected
                              //     sends Profile 1 - 14 commands to OSSC. Must have IR LED emitter connected.
                              //     
                              // 2 = enabled for gscart switch only (remote profiles 1-8 for first gscart, 9-14 for first 6 inputs on second gscart)

uint8_t const MTVir = 0;   // Must have IR "Receiver" connected to the Donut Dongle for option 1 & 2.
                              // 0 = disables IR Receiver -> Serial Control for MT-VIKI 8 Port HDMI switch
                              //
                              // 1 = MT-VIKI 8 Port HDMI switch connected to "Extron sw1"
                              //     Using the RT4K Remote w/ the IR Receiver, AUX8 + profile button changes the MT-VIKI Input over Serial.
                              //     Sends auxprof SVS profiles listed below.
                              //
                              // 2 = MT-VIKI 8 Port HDMI switch connected to "Extron sw2"
                              //     Using the RT4K Remote w/ the IR Receiver, AUX8 + profile button changes the MT-VIKI Input over Serial.
                              //     Sends auxprof SVS profiles listed below. You can change them below to 101 - 108 to prevent SVS profile conflicts if needed.
                              // 3 = MT-VIKI 8 Port HDMI switch connected to BOTH "alt sw1" and "alt sw2"
                              //     Use AUX7 and AUX8 buttons as described above.
                              //

uint8_t const TESmartir = 0;  // Must have IR "Receiver" connected to the Donut Dongle for option 1 and above.
                              // 0 = disables IR Receiver -> Serial Control for TESmart 16x1 Port HDMI switch
                              //
                              // 1 = TESmart 16x1 HDMI switch connected to "alt sw1"
                              //     Using the RT4K Remote w/ the IR Receiver, AUX7 + profile button changes the Input over Serial. AUX7 + AUX1 - AUX4 for Input 13 - 16.
                              //     Sends SVS profile 1 - 16 as well.
                              //
                              // 2 = TESmart 16x1 HDMI switch connected to "alt sw2"
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
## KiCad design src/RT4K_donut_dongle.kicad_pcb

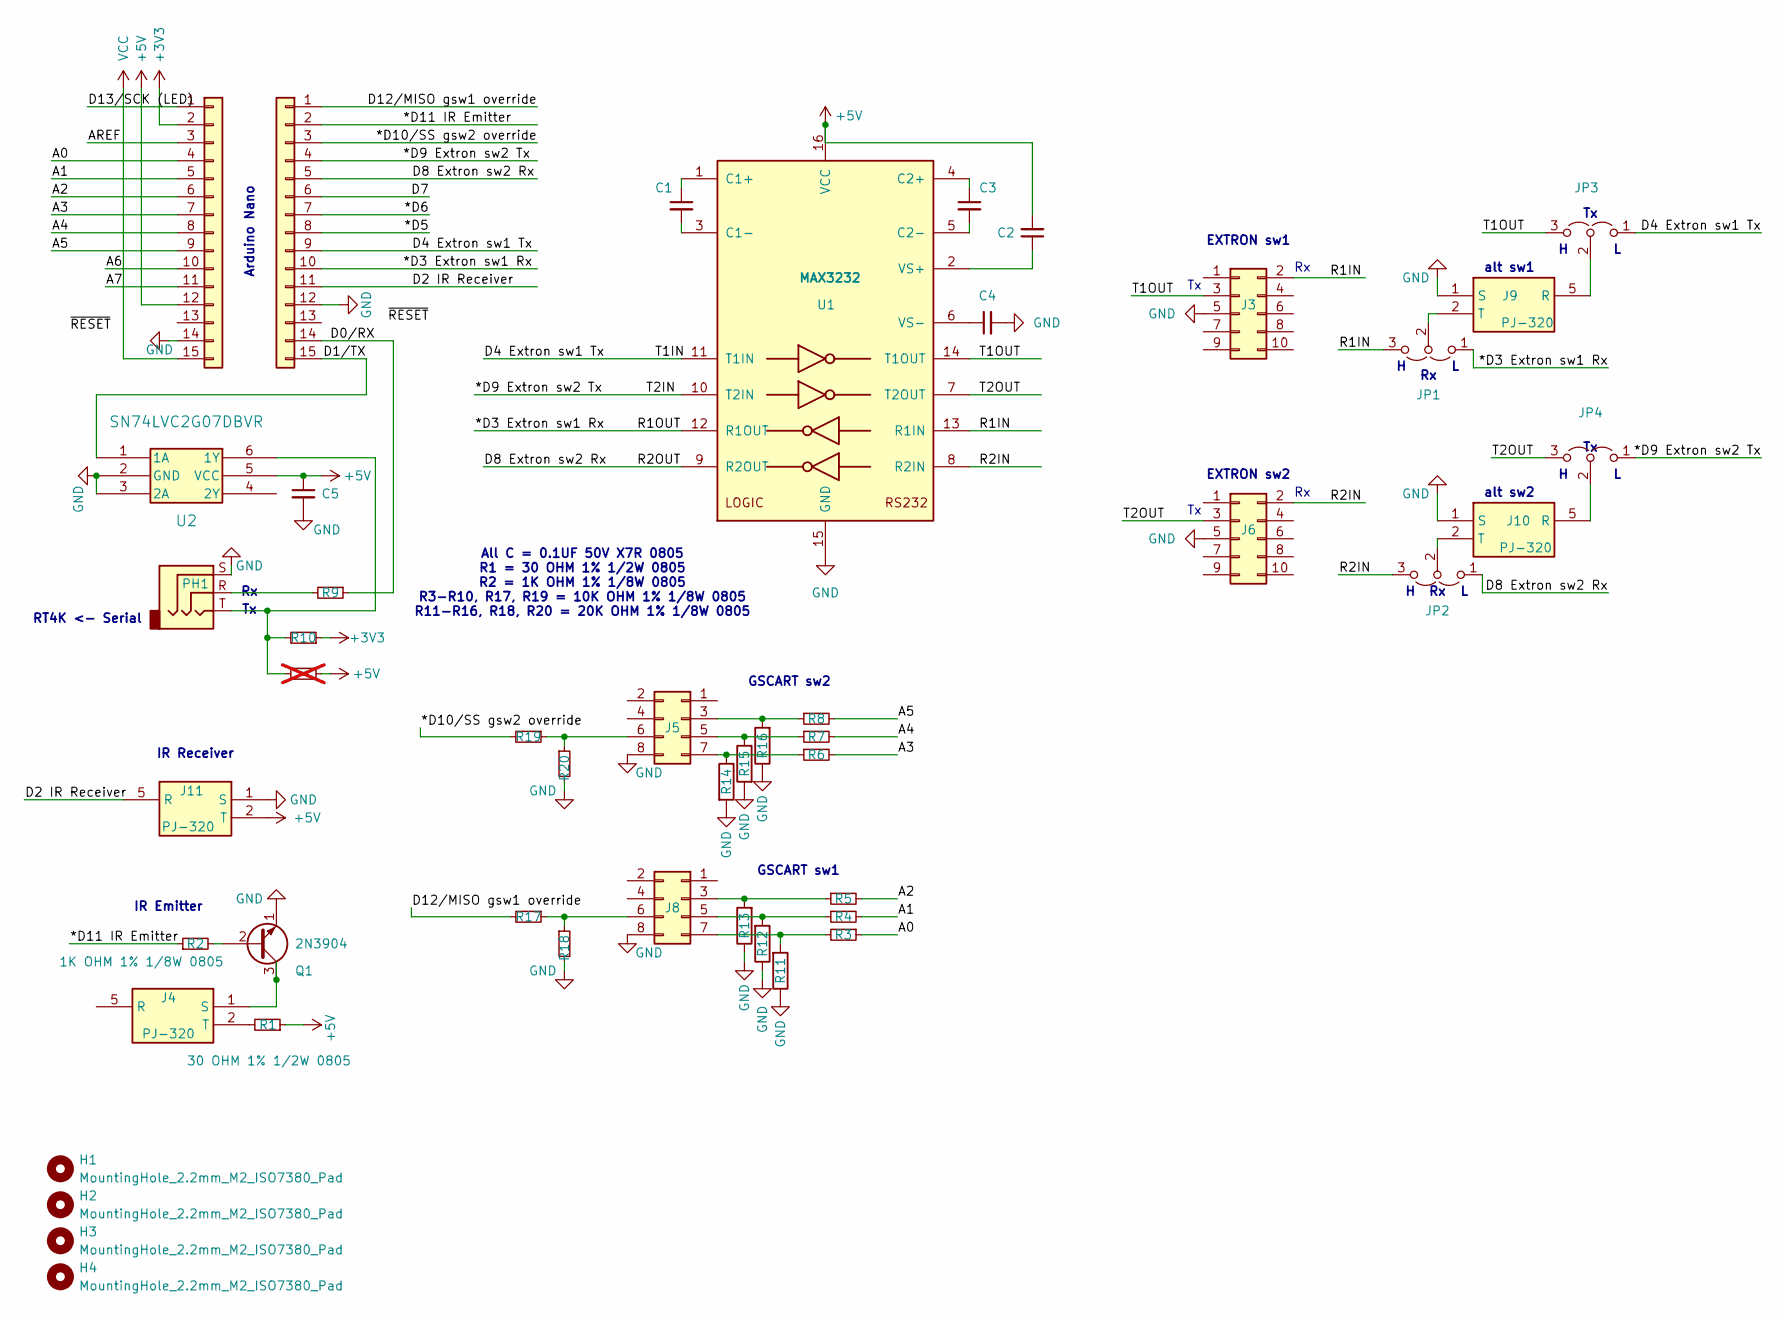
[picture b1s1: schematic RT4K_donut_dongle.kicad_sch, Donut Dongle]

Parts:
C1, C2, C3, C4, C5: 0.1UF 50V X7R 0805; C_0805_2012Metric_Pad1.18x1.45mm_HandSolder
H1, H2, H3, H4: MountingHole_2.2mm_M2_ISO7380_Pad
J1, J2: 2.54mm Pitch Single Row Female 15P Header Strip; PinSocket_1x15_P2.54mm_Vertical
J3, J6: 2x5 Pin Double Row 2.54mm Pitch Straight Box Head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; IDC-Header_2x05_P2.54mm_Vertical
J4, J9, J10, J11: PJ-320; SJ335083ATR; Mouser Part Number 179-SJ3-35083A-TR
J5, J8: 2x4 Pin Double Row 2.54mm Pitch Straight Box Head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; IDC-Header_2x04_P2.54mm_Vertical
JP1, JP2: Jumper_3_Open; PinHeader_1x03_P2.54mm_Vertical
JP3, JP4: PinHeader_1x03_P2.54mm_Vertical
PH1: PJ-307; Jack_3.5mm_CUI_SJ1-3525N_Horizontal
Q1: 2N3904; TO-92_Inline
R1: 30 OHM 1% 1/2W 0805; R_0805_2012Metric_Pad1.20x1.40mm_HandSolder
R2: 1K OHM 1% 1/8W 0805; R_0805_2012Metric_Pad1.20x1.40mm_HandSolder
R3, R4, R5, R6, R7, R8, R9, R10, R17, R19: 10K OHM 1% 1/8W 0805; R_0805_2012Metric_Pad1.20x1.40mm_HandSolder
R11, R12, R13, R14, R15, R16, R18, R20: 20K OHM 1% 1/8W 0805; R_0805_2012Metric_Pad1.20x1.40mm_HandSolder
R21: 10K OHM 1% 1/8W 0805; R_0805_2012Metric_Pad1.20x1.40mm_HandSolder; not fitted
U1: MAX3232; SOIC-16W_5.3x10.2mm_P1.27mm
U2: SN74LVC2G07DBVR; TSOT-23-6_HandSoldering

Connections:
+3V3: J1.2, R10.1
+5V: C2.2, C5.1, J1.12, J11.2 (T), R1.1, R21.1, U1.16 (VCC), U2.5 (VCC)
/*D3 Extron sw1 Rx: J2.10, JP1.1 (A), U1.12 (R1OUT); also elsewhere on the board
/*D9 Extron sw2 Tx: J2.4, JP4.1 (A), U1.10 (T2IN); also elsewhere on the board
/*D10/SS gsw2 override: J2.3, R19.2; also elsewhere on the board
/*D11 IR Emitter: J2.2, R2.1; also elsewhere on the board
/A0: J1.4, R3.1
/A1: J1.5, R4.2
/A2: J1.6, R5.2
/A3: J1.7, R6.2
/A4: J1.8, R7.2
/A5: J1.9, R8.2
/A6: J1.10
/A7: J1.11
/AREF: J1.3
/D0/RX: J2.14, R9.1; also elsewhere on the board
/D1/TX: J2.15, U2.1 (1A); also elsewhere on the board
/D2 IR Receiver: J2.11, J11.5 (R); also elsewhere on the board
/D4 Extron sw1 Tx: J2.9, JP3.1 (A), U1.11 (T1IN); also elsewhere on the board
/D8 Extron sw2 Rx: J2.5, JP2.1 (A), U1.9 (R2OUT); also elsewhere on the board
/D12/MISO gsw1 override: J2.1, R17.2; also elsewhere on the board
/D13/SCK (LED): J1.1
/R1IN: J3.2, JP1.3 (B), U1.13 (R1IN)
/R2IN: J6.2, JP2.3 (B), U1.8 (R2IN)
/T1OUT: J3.3, JP3.3 (B), U1.14 (T1OUT)
/T2OUT: J6.3, JP4.3 (B), U1.7 (T2OUT)
GND: C4.2, C5.2, J1.14, J2.12, J3.5, J5.8, J6.5, J8.8, J9.1 (S), J10.1 (S), J11.1 (S), PH1.S, Q1.1 (E), R11.1, R12.1, R13.1, R14.2, R15.2, R16.1, R18.2, R20.2, U1.15 (GND), U2.2 (GND), U2.3 (2A); also elsewhere on the board
unnamed: J4.1 (S), Q1.3 (C)
unnamed: J4.2 (T), R1.2
unnamed: J5.3, R8.1, R16.2
unnamed: J5.5, R7.1, R15.1
unnamed: J5.6, R19.1, R20.1
unnamed: J5.7, R6.1, R14.1
unnamed: J8.3, R5.1, R13.2
unnamed: J8.5, R4.1, R12.2
unnamed: J8.6, R17.1, R18.1
unnamed: J8.7, R3.2, R11.2
unnamed: J9.5 (R), JP3.2 (C)
unnamed: J9.2 (T), JP1.2 (C)
unnamed: J10.5 (R), JP4.2 (C)
unnamed: J10.2 (T), JP2.2 (C)
unnamed: PH1.R, R9.2
unnamed: Q1.2 (B), R2.2
unnamed: C1.1, U1.1 (C1+)
unnamed: C1.2, U1.3 (C1-)
unnamed: C3.1, U1.4 (C2+)
unnamed: C3.2, U1.5 (C2-)
unnamed: C2.1, U1.2 (VS+)
unnamed: C4.1, U1.6 (VS-)
unnamed: PH1.T, R10.2, R21.2, U2.6 (1Y)
VCC: J1.15

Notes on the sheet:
EXTRON sw2
GSCART sw2
RT4K <- Serial
Arduino Nano
EXTRON sw1
IR Receiver
IR Emitter
alt sw2
GSCART sw1
alt sw1
All C = 0.1UF 50V X7R 0805 R1 = 30 OHM 1% 1/2W 0805 R2 = 1K OHM 1% 1/8W 0805 R3-R10, R17, R19 = 10K OHM 1% 1/8W 0805 R11-R16, R18, R20 = 20K OHM 1% 1/8W 0805

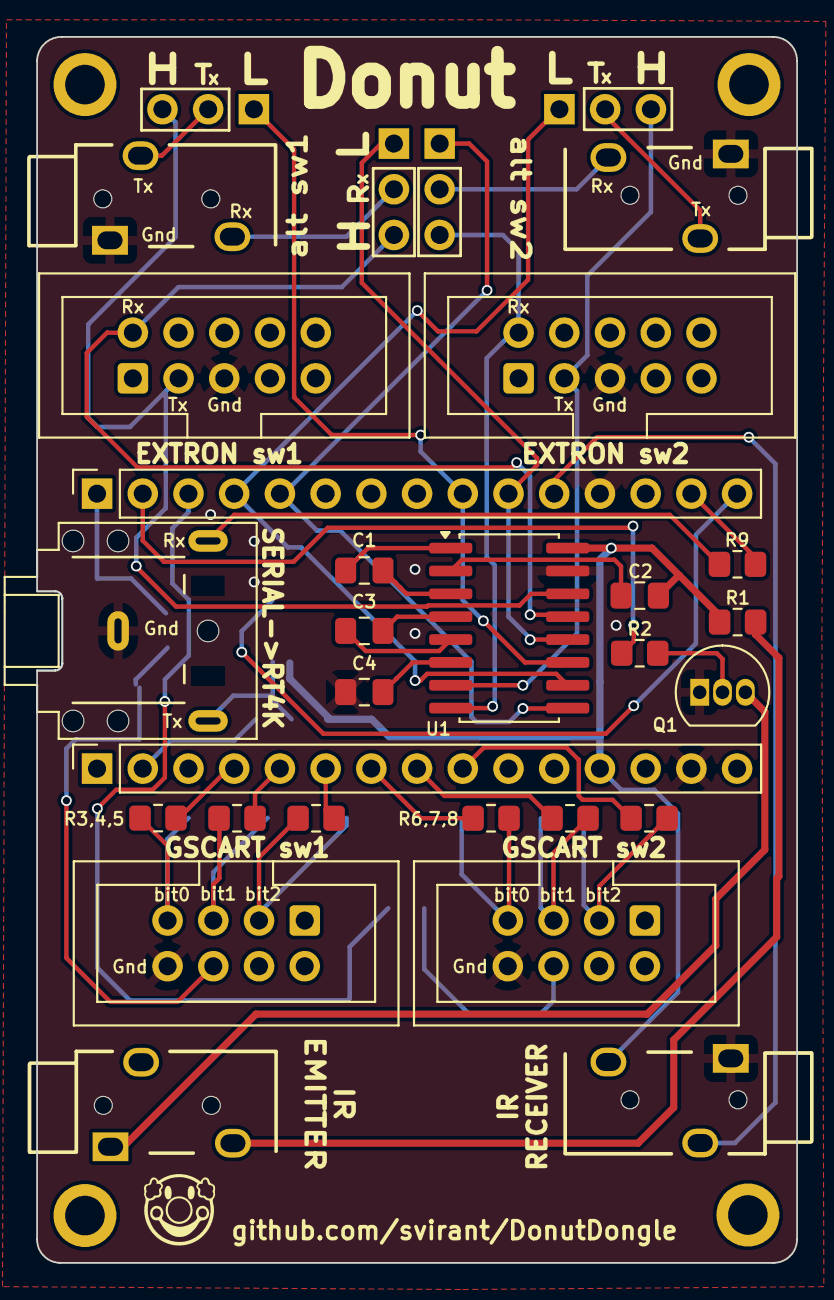
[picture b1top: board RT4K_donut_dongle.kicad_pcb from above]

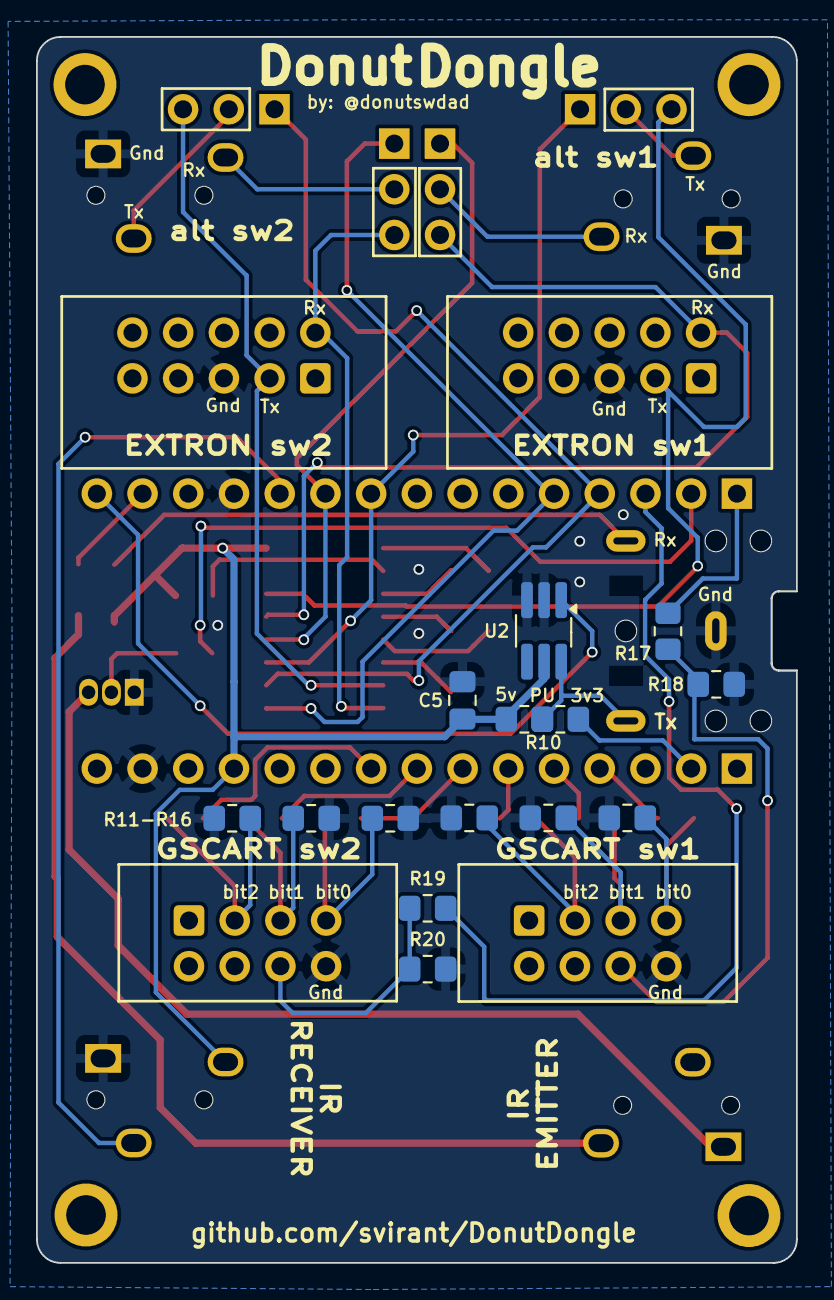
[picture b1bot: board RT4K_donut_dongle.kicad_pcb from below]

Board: 2 copper layers, 42.2 x 68.1 mm, 48 parts (14 on the bottom side), 46 nets.

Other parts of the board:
J1#2: 2.54mm Pitch Single Row Female 15P Header Strip; PinSocket_1x15_P2.54mm_Vertical

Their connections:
/*D3 Extron sw1 Rx: J1#2.10; also elsewhere on the board
/*D9 Extron sw2 Tx: J1#2.4; also elsewhere on the board
/*D10/SS gsw2 override: J1#2.3; also elsewhere on the board
/*D11 IR Emitter: J1#2.2; also elsewhere on the board
/D0/RX: J1#2.14; also elsewhere on the board
/D1/TX: J1#2.15; also elsewhere on the board
/D2 IR Receiver: J1#2.11; also elsewhere on the board
/D4 Extron sw1 Tx: J1#2.9; also elsewhere on the board
/D8 Extron sw2 Rx: J1#2.5; also elsewhere on the board
/D12/MISO gsw1 override: J1#2.1; also elsewhere on the board
GND: J1#2.12; also elsewhere on the board

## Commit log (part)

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2025-01-28 updated ibom
2025-01-29 gscart override future proofing, bom update
2025-01-29 updated gscart_ext_connector to support override
2025-01-30 bom update
2025-02-01 added gscart override and support for multiple DD. SVS profiles are now default
2025-02-01 added SVS Profile numbering scheme section fix
2025-02-03 updated "Advanced" options section
2025-02-03 restored aux5,6 buttons when gctl is off
2025-02-04 VGAPassthrough with "shared serial bus" now standard
2025-02-05 blink builtin led while waking RT4K from sleep
2025-02-05 waking RT4K with remote will also resend the current profile after it's finished waking
2025-02-05 blink builtin led while waking RT4K from sleep (revert ability to cancel)
2025-02-05 typo
2025-02-06 renamed function, fixed RT4K IR S0_ logic
2025-02-07 optimized sendSVS function
2025-02-07 moved IRsend into separate function, variable reorg
2025-02-07 AUX8 + Power button can power cycle a TV via IR emitter
2025-02-07 updated New IR Remote Control functionality section with TV power control
2025-02-09 code cleanup part duex
2025-02-10 include SVS = 2 in S0 logic
2025-02-10 improved gscart/gcomp experimental override logic
2025-02-10 tweaked auto to manual gscart/gcomp experimental override logic
2025-02-15 made pin toggle code more readable++
2025-02-19 RC1 for Donut Dongle, all files needed have been uploaded
2025-02-19 renaming RT4K_donut_dongle.zip RT4K_donut_dongle_rc1.zip
2025-02-20 added pcb and schematic images for RC1
2025-02-21 updated layout examples
2025-02-25 added OSSC profile support
2025-02-25 optimized OSSC IR code sequences
2025-02-27 new! Donut Dongle case & updated imagery, formatting
2025-02-27 info regarding RT5x support, must be on firmware 3.7 or higher
2025-02-27 gscart/gcomp manual mode is now totally disabled when set as so. comments added about RT5x 3.7 firmware required for use
2025-02-27 gcomp/gscart override test
2025-02-28 gscart/gcomp override, low to enable
2025-02-28 gscart / gcomp manual input selection verified working for vers 5.x switches, must enable with gctl = 1
2025-02-28 added legacy 5x remote support for gscart/gcomp input selection
2025-02-28 added diffused clown nose image
2025-03-12 RC2 DD pcb released. No major changes, RC1 can easily be modified. See Assembly section.
2025-03-13 updated ibom images to reflect RC2 pcb
2025-03-13 updated RC2 info
2025-03-16 updated BOM notes
2025-03-20 added "return" character before every serial command to clear out buffer. needed when sharing TX bus with other devices.
2025-03-20 added VGA Adapter pictures
2025-03-30 Thanks to section, layout changes
2025-03-30 Thanks section, typos
2025-04-03 RC2 is now v1.0
2025-04-11 added 3D Printed VGA Adapter Case
2025-04-11 updated Thanks to section
2025-04-17 cleanup
2025-04-24 v1.1 - added TESmart 16x1 control via RT4K remote
2025-04-27 added support for TESmart 4K30 16x1 switch
2025-04-30 updated Extron support info
2025-06-26 new smaller YC2VGA wSerial adapter
2025-06-26 fixed Note related to ko-fi shop
2025-07-09 updated BOM on MT-VIKI / DB9 to 3.5mm adapter
2025-07-09 added 3DP housing for MT-VIKI / Extron / DB9 to 3.5mm adapter
2025-07-11 updated supports
2025-07-14 new extron auto matrix feature. enable in options and set desired output port and number of inputs.
2025-07-14 fixed bug where auto matrix mode on SW2 sent same profiles as SW1
2025-07-14 updated defaults
2025-07-15 fixed Presets sometimes not being detected. auto switching can now be set to output to ALL outputs.
2025-07-15 previous Presets bug should now also be fixed for matrix switches that report In00 vs In0
2025-07-16 fixed logic in setTie() so that it only removes the ties it creates
2025-07-16 new option for auto matrix input to trigger a Preset so the outputs can be unique for each input. defined in vinMatrix option
2025-07-18 more memory tweaks, fixed setTie bug leftover from downsizing to 16 from 32 input/outputs
2025-07-19 fixed recallPreset() typo
2025-07-28 added troubleshooting section
2025-08-08 update MT-VIKI "New IR Remote Control functionality" section
2025-08-09 added more info about the Otaku mod
2025-08-12 IR code for LG TV power button should now be more compatible with other LG TVs
2025-08-15 added notes about new _beta support for MT-VIKI. Thanks to Arthrimus!
2025-08-15 code and comments cleanup
2025-08-18 update comments
2025-08-21 logic tweaks
2025-10-02 updated Bambu Studio settings for higher quality print
2025-10-22 bug found in MT-VIKI face button logic that would cause sw2 to also respond even when not being used
2025-10-22 updated with only one wall on top surfaces in slicer
2025-10-23 updated Schematic png and layout
2025-10-27 updated remote receiver to respond to AUX4 = Color Correction menu shortcut, AUX5 = Audio menu shortcut. If using "gctl = 1" to manually change gscart/comp switch inputs, Press "AUX5" twice for Audio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
2025-11-20 reverted to previous reliable method of power toggle for LG CX OLED
2025-12-10 adds MT-VIKI disconnection detection
2026-01-08 support for the Extron SW4 VGA Ars confirmed
2026-01-18 merged Donut_Dongle_Extron_AutoMatrix_beta.ino back into Donut_Dongle_beta.ino v1.6
2026-01-18 added support for older Extron Crosspoints for when S0 is also enabled
2026-01-18 further reduced memory footprint using PROGMEM for const variables
2026-01-18 alternate format for 3D printing services
2026-01-18 fixed command sent when "RECONFIG" is received from Extron switchers
2026-01-18 For older Extron Crosspoints, where "RECONFIG" is sent when changes are made, the profile is only changed when a different input is selected for the defined output.
    Without this, the profile would be resent when changes to other outputs are selected.
2026-01-18 expanded capture for Extron "OUT IN All" messages
2026-01-19 removed test remnants, updated RECONFIG response to be a single serial.write() while staying memory efficient
2026-01-19 updated setup guide
2026-01-20 added PROGMEM is select spots to further reduce SRAM consumption. automatrix now supports 32 inputs.
2026-01-21 rewrote functions to be PROGMEM compatible. fixed bug in automatrix mode.
2026-01-22 Redo of options for (vinMatrix) auto matrix mode. Uses far less memory due to use of compiling directives. Removed all use of PROGMEM for speed.
2026-01-22 updated to match the latest Donut Dongle beta in features
2026-01-24 added toggle for the option to load Profile when no gameID has been found
2026-01-24 minor tweaks
2026-01-25 added ability to turn off checking consoles for gameID. each console in the list is checked for 2 seconds before moving on to the next one. uncheck powered off ones to speed up the loop.
2026-01-25 cleaned up UI. increased gTime to 4s
2026-01-25 minor tweak
2026-01-27 add tooltips to web ui. code cleanup.
2026-01-27 automatrixSW1 directive updated
2026-01-28 now using LittleFS
2026-01-29 make status icon updates more resilient
2026-01-30 potential fix for mt-viki regression lockup bug
2026-02-04 when all consoles are off on a switch, will change profiles back to the another switch that still has active consoles. can fallback to/from SW1, SW2, GSCART1, GSCART2
2026-02-04 moved back to main.
2026-02-04 gameID is now part of the "fallback" system, which is where when all inputs are off on a switch, or no gameIDs can be found, a profile change to the previous connected switch with an active input wil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
2026-02-05 fixed some edge cases with GAMEID profile changes
2026-02-07 This update prevents the "S0" or "remote prof12" profile from constantly overriding any profile loaded with the remote when all consoles are off and S0 set true.
2026-02-07 fallback keeps track of switch order
2026-02-09 "Auto Matrix" feature now remembers input "On" order for fallback. IRsend calls now happen inside sendProfile function. HUGE memory savings.
2026-02-10 OTA updates are now available over Wifi in Arduino IDE 2.x. donutshop will now show up as a network port in "Ports". wifi / creds have moved to the top of file. other minor tweaks.
2026-02-10 tweaked web ui elements.
2026-02-11 USB Serial Host mode can now be used instead to send Serial Commands. set "usbMode" to true. requires additional library and OTG adapter.
2026-02-12 fixed a bug where when S0 = true, profiles changed with the IR remote would not stick
2026-02-12 fixed a MT-VIKI bug where when S0 = true, profiles changed with the IR remote would not stick
2026-02-13 tweaked rmt use logic
2026-02-13 S0 logic is ignored when in gameID only mode
2026-02-16 new Settings page can configure most of the settings live w/o needing to reflash. You still need to reflash if ever enabling USB Host Mode or AutoMatrix
2026-02-17 auto matrix mode now supported in web ui. code cleanup.
2026-02-18 automatically sets automatrix switch to Verbose 3 if the switch reboots. double press of AUX8 + Power button also sends IR to power toggle a TV.
2026-02-18 usbHost mode now on by default. controlled by "#define usbMode". Serial continues to work over VGA. Automatically sets Extron Matrix Switch in autoswitch mode to Verbose 3 if it reboots.
2026-02-18 Captive Portal design tweak
2026-02-18 added .bin firmware udpate file for updates via web ui.
2026-02-19 added support for MCP 2.0+ firmware devices. fixed hostname for new WifiManager.
2026-02-19 fixed sendSVS command over VGA Serial when usbMode = true. added new Mode so same code base can be used for DonutShop project and hide irrelevant settings.
2026-02-21 remote is now more responsive when MT-VIKI disconnection detection is on
2026-02-24 gameID consoles now fallback in the order in which they were powered on. removed delays in certain functions.
2026-02-24 memory heap precautionary safeguard
2026-02-25 converted all String types to char[] arrays for minimal memory heap usage
2026-02-26 Uptime is now displayed in Settings under Firmware section
2026-03-01 fixed long standing bug that would have caused changing inputs on the MT-VIKI via RT4K remote to not work in certain scenarios
2026-03-02 removed older versions
2026-03-10 new flashing / setup instructions
2026-03-13 fixed regression bug for Extron switches that respond with single digit input. Ex: "In1 " vs "In01"
2026-04-19 Alternate SVS profile system added
2026-04-23 added Alternate SVS Profile System. support for dasiy-chained Otaku modded switches. MT-VIKI power on defaults tweaked.
2026-04-23 hotfix for IR Emitter
2026-04-23 Updated instructions to be specific to Donut_Dongle_gameID
2026-04-25 the "SAFE" button is now used instead of AUX8 for changing aux profiles. Info updated in "New IR Remote Control functionality" section.
2026-04-25 SAFE button has replaced AUX8 button when used to change auxprof with the IR remote. MT-VIKI control options have been updated.
2026-04-27 added web ui image
2026-05-14 usbMode is on now by default as it does not affect VGA serial mode being used at the same time. disabled wifi power saving mode. updated support for older Extrons.
2026-06-05 added simple Telnet server. added RT4K Terminal in "Settings" section of DonutShop. (Remote Control Commands are relayed to RT4K) Navigation of the RT4K menu is possible with keyboard keys. Replaced 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
2026-06-05 added features to RT4K Terminal. "help / ?" shows commands available.
2026-06-06 renamed correctly
2026-06-12 more options added to keyboard navigation. terminal focus added. gameID lookup tweaks.
2026-06-19 in keyboard nav mode, undefined keys no longer reside in prompt.
